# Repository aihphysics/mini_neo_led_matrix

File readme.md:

# Neo LED

## Description
* A simple PCB for mounting SMD 1010 adafruit 4492 neopixels.
* 2 pin input, 5V DC and data line, 
* Should be drivable with V_{cc} from a pi pico, pro micro, etc.
* Simple grid pattern.
* Should evolve in future, expand to more LED, MCU on board, button cell clasp etc.

## Photos
Here's the circuit diagram, things should be decently specced here, nothing but to test the real thing!

The current PCB design, this ones more of a work in progress : )

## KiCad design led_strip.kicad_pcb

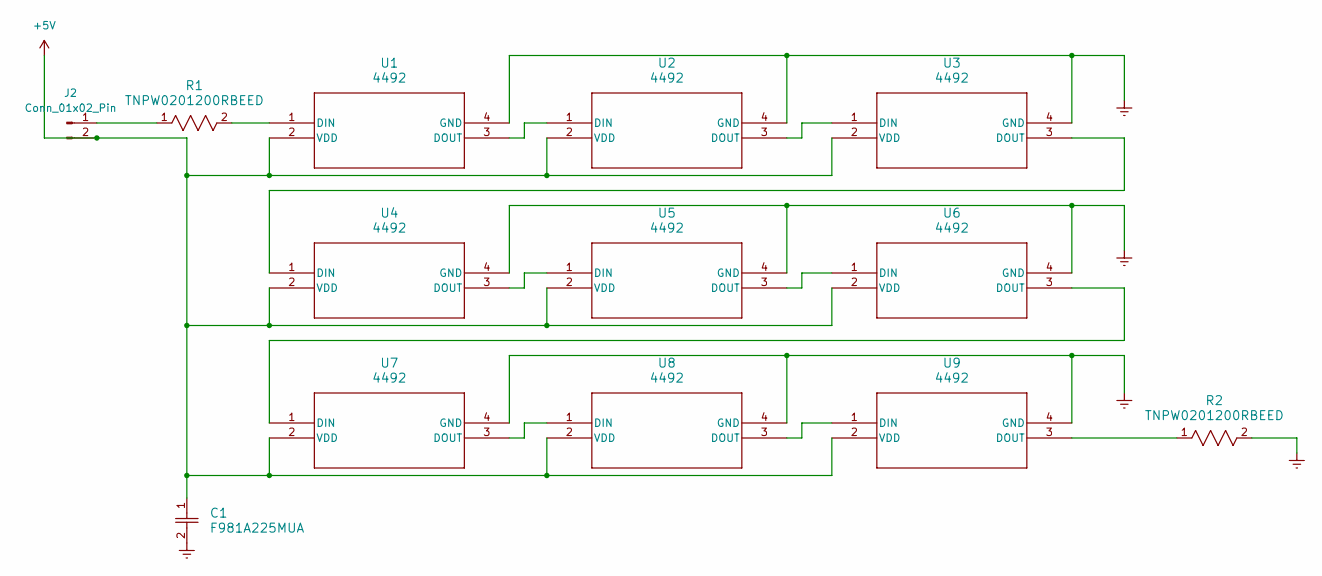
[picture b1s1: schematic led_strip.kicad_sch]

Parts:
C1: F981A225MUA; CAP_A225MUA_AVX
J2: Conn_01x02_Pin; PinHeader_1x02_P2.54mm_Vertical
R1, R2: TNPW0201200RBEED; RES_TNPW0201_VIS
U1, U2, U3, U4, U5, U6, U7, U8, U9: 4492; 4492_ADA

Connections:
+5V: C1.1, J2.2, U1.2 (VDD), U2.2 (VDD), U3.2 (VDD), U4.2 (VDD), U5.2 (VDD), U6.2 (VDD), U7.2 (VDD), U8.2 (VDD), U9.2 (VDD)
Earth: C1.2, R2.2, U1.4 (GND), U2.4 (GND), U3.4 (GND), U4.4 (GND), U5.4 (GND), U6.4 (GND), U7.4 (GND), U8.4 (GND), U9.4 (GND)
unnamed: J2.1, R1.1
unnamed: R1.2, U1.1 (DIN)
unnamed: U1.3 (DOUT), U2.1 (DIN)
unnamed: U2.3 (DOUT), U3.1 (DIN)
unnamed: U3.3 (DOUT), U4.1 (DIN)
unnamed: U4.3 (DOUT), U5.1 (DIN)
unnamed: U5.3 (DOUT), U6.1 (DIN)
unnamed: U6.3 (DOUT), U7.1 (DIN)
unnamed: U7.3 (DOUT), U8.1 (DIN)
unnamed: U8.3 (DOUT), U9.1 (DIN)
unnamed: R2.1, U9.3 (DOUT)

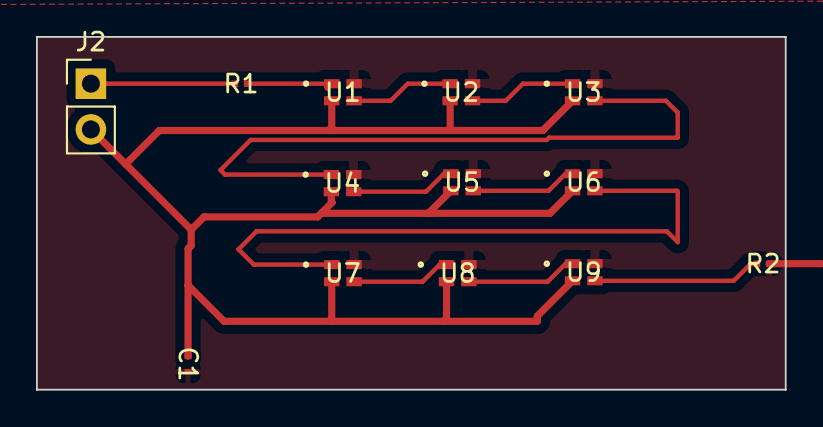
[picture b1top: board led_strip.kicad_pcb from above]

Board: 2 copper layers, 41.6 x 19.6 mm, 13 parts (0 on the bottom side), 13 nets.

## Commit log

2023-07-27 gitification of led pcb project
2023-07-27 readme and assets
2023-07-27 small updates
